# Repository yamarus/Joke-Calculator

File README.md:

# Joke Calculator for an Economist

A homemade birthday gift for an economist: a calculator that understands the maths but makes questionable economic forecasts. It has a round colour display, physical keys, and a habit of treating uncertainty as an opportunity.

I started just five days before the birthday, so I used off-the-shelf components and made the board and enclosure at home. The firmware was vibe-coded with ChatGPT, then tested on the device.

## What it does

- **Normal:** a scientific calculator with fractions, powers, roots, logarithms, trig, DEG/RAD and Ans.
- **Uncertainty:** enter a value with its standard uncertainty, such as `100 ± 3`. The calculator propagates independent uncertainties using first-order derivatives.
- **Economics:** ordinary input. Values receive artificial, random uncertainties → the expression propagates them → the result becomes a slightly unreliable economic estimate.

The economic estimate shifts by a multiple of sigma. Its absurdity score depends on uncertainty relative to the result, cancellation, risky division and nonlinear growth. More uncertainty gives the calculator more room to misbehave. Input assumptions stay stable within a session; repeated `=` can revise the presentation.

Three personalities share that machinery: **Economist** cautiously estimates; **TV Expert** becomes more confident as the evidence gets worse; **Referee 2** finds methodological objections. Settings control idle shutdown, displayed digits and notation, and survive reboot.

**Controls:** MODE cycles Normal → Economics → Uncertainty → Settings. FN activates the secondary legends for one keypress; left/right move between expression fields, and FN + `=` advances to the next field. In Uncertainty mode, `±` enters sigma; in Normal and Economics it changes the sign. AC clears, DEL edits, and repeated `=` in Economics revisits the same model with a fresh interpretation.

Some examples of what might happen:

Usually Economics mode simply produces a plausible estimate with uncertainty, without an extra joke. Here, `48/6` becomes `7.921 ± 0.4328`:

| Unreliable growth forecast | An imaginary economic precedent |
| --- | --- |
|  |  |
| `1.08^18`: TV Expert may hide the uncertainty and insist it is **VERY CLEAR**. | `sqrt(-1)`: **2002 Ig Nobel got there first.** No complex arithmetic, just a purple `i`. |

| A denominator nobody should trust| Excellent use of equipment |
| --- | --- |
| |  |
| `1/(1000-999)`: strong cancellation can make the denominator statistically compatible with zero and invite a Black Swan. | `80085`: **Very mature.** The exact-number banner is intentional. |

These screenshots illustrate possible responses; probabilistic events do not appear every time. More examples and their trigger conditions are in the [PDF gallery](docs/econ-gallery.pdf). ECON's random function also returns exactly `1 ± 0`.

## Electronics and homemade PCB

The design is deliberately minimal: a **CH32V006F8P7**, a **GC9A01 240×240 SPI LCD**, a battery, an AliExpress battery charging/protection board, and a handful of passive components plus an LCD power switch. The keyboard is a 6×5 switch matrix. No framebuffer is needed.

The PCB was made at home: laser-print the pattern on glossy paper, iron the toner onto copper-clad board, then etch it using hair-bleach developer. The MCU was reflow-soldered on a frying pan; the remaining components were soldered by hand. These photos document the build, rather than a chemical or temperature recipe.

| Etched board | MCU soldered | Remaining components |
| --- | --- | --- |
|  |  |  |

The [KiCad schematic and PCB](kicad/) are included. The schematic uses a **CH32V003FxPx symbol**, while this firmware targets **CH32V006F8P7**; check that distinction when reproducing the board.

| Connection | MCU pin(s) |
| --- | --- |
| LCD SCK / MOSI / DC | PC5 / PC6 / PC7 |
| LCD power, active low | PD4 |
| Keyboard rows | PD6, PA1, PC0, PD0, PA2, PC1 |
| Keyboard columns | PC2, PC3, PC4, PD2, PD3 |
| Power button, active low | PD5 |

LCD CS/RST are not connected. A short power-button press enters standby; the next press wakes it. Holding the button for about two seconds resets the MCU through its interrupt handler, even if the main loop hangs.

## Case and buttons

Printed on a **Bambu Lab A1 mini with a single filament at a time**. The colours came from manually changing filament after the first four layers, rather than using a multicolour attachment.

The first button printed after a filament change tended to have a defect. Print at least two buttons on the bed and use one as a sacrificial purge piece; keep the good one.

The [3MF project](calculator.3mf) is included.

## Build and flash

Use the **WCH RISC-V GCC12 toolchain supplied with MounRiver Studio**. The build uses WCH's `rv32ec_zmmul_xw` ISA and `ilp32e` ABI; a generic RISC-V compiler is not interchangeable.

```sh
make WCH_BIN="/path/to/WCH/GCC12/bin"
make size WCH_BIN="/path/to/WCH/GCC12/bin"
```

Outputs are `build/calculator.bin`, `.hex` and `.elf`. If the WCH tools are on PATH, plain `make` works. I programmed the MCU using Ardulink on an Arduino Nano board. The supplied flashing script uses minichlink with your programmer's serial port:

```sh
./flash.sh build/calculator.bin /dev/your-programmer-port
```

The firmware uses about **61.7 KiB of flash** and **1.9 KiB of static RAM**, plus a 3 KiB reserved stack. The last 256-byte flash page stores settings. Flash space is almost full; toolchain changes can affect whether the build fits.

`User/` contains the application; `Core/`, `Debug/`, `Startup/` and `Peripheral/` supply the required WCH support. Only used peripheral driver implementations are included. Generated font data is supplied, so building needs no font-generation tools.

WCH files retain their original copyright and usage notices. The DejaVu font notice is in [licenses/LICENSE_DEJAVU](licenses/LICENSE_DEJAVU). No additional license for the original project files has been selected yet.

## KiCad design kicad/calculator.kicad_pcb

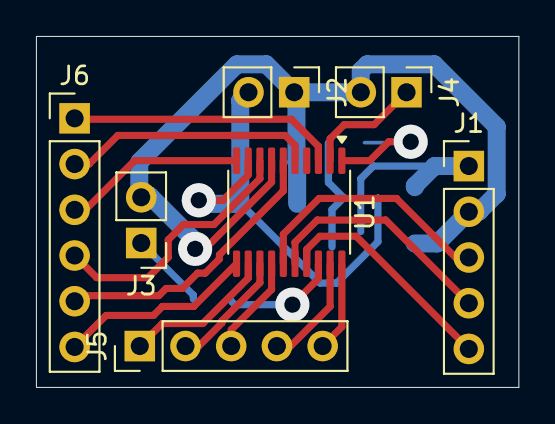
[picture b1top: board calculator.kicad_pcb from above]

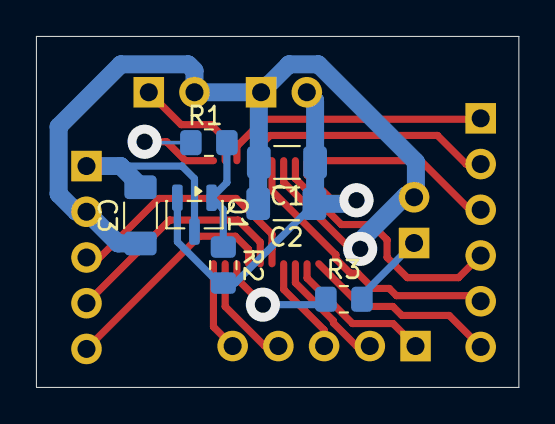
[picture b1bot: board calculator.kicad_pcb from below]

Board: 2 copper layers, 26.8 x 19.5 mm, 14 parts (7 on the bottom side), 22 nets.

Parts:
C1: 2.2uF; C_1206_3216Metric_Pad1.33x1.80mm_HandSolder
C2: 100nF; C_1206_3216Metric_Pad1.33x1.80mm_HandSolder
C3: 10uF; C_1206_3216Metric_Pad1.33x1.80mm_HandSolder
J1, J5: Conn_01x05; PinHeader_1x05_P2.54mm_Vertical
J2, J3, J4: Conn_01x02; PinHeader_1x02_P2.54mm_Vertical
J6: Conn_01x06; PinHeader_1x06_P2.54mm_Vertical
Q1: AO3401A; SOT-23
R1: 82; R_0805_2012Metric_Pad1.20x1.40mm_HandSolder
R2: 43k; R_0805_2012Metric_Pad1.20x1.40mm_HandSolder
R3: 1.8k; R_0805_2012Metric_Pad1.20x1.40mm_HandSolder
U1: CH32V003FxPx; TSSOP-20_4.4x6.5mm_P0.65mm

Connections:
/C0: J5.1, U1.12 (PC2)
/C1: J5.2, U1.13 (PC3)
/C2: J5.3, U1.14 (PC4)
/C3: J5.4, U1.19 (PD2)
/C4: J5.5, U1.20 (PD3)
/DC: J1.5, U1.17 (PC7)
/DVCC: C3.2, J1.1, Q1.3 (D)
/R0: J6.1, U1.3 (PD6)
/R1: J6.2, U1.5 (PA1)
/R2: J6.3, U1.10 (PC0)
/R3: J6.4, U1.8 (PD0)
/R4: J6.5, U1.6 (PA2)
/R5: J6.6, U1.11 (PC1)
/SCL: J1.3, U1.15 (PC5)
/SDA: J1.4, U1.16 (PC6)
/SWIO: R3.1, U1.18 (PD1)
/TX: J4.1, U1.2 (PD5)
GND: C1.2, C2.2, C3.1, J1.2, J2.1, J3.2, J4.2, U1.7 (VSS)
unnamed: J3.1, R3.2
unnamed: Q1.1 (G), R1.2, R2.1
unnamed: R1.1, U1.1 (PD4)
VCC: C1.1, C2.1, J2.2, Q1.2 (S), R2.2, U1.9 (VDD)
